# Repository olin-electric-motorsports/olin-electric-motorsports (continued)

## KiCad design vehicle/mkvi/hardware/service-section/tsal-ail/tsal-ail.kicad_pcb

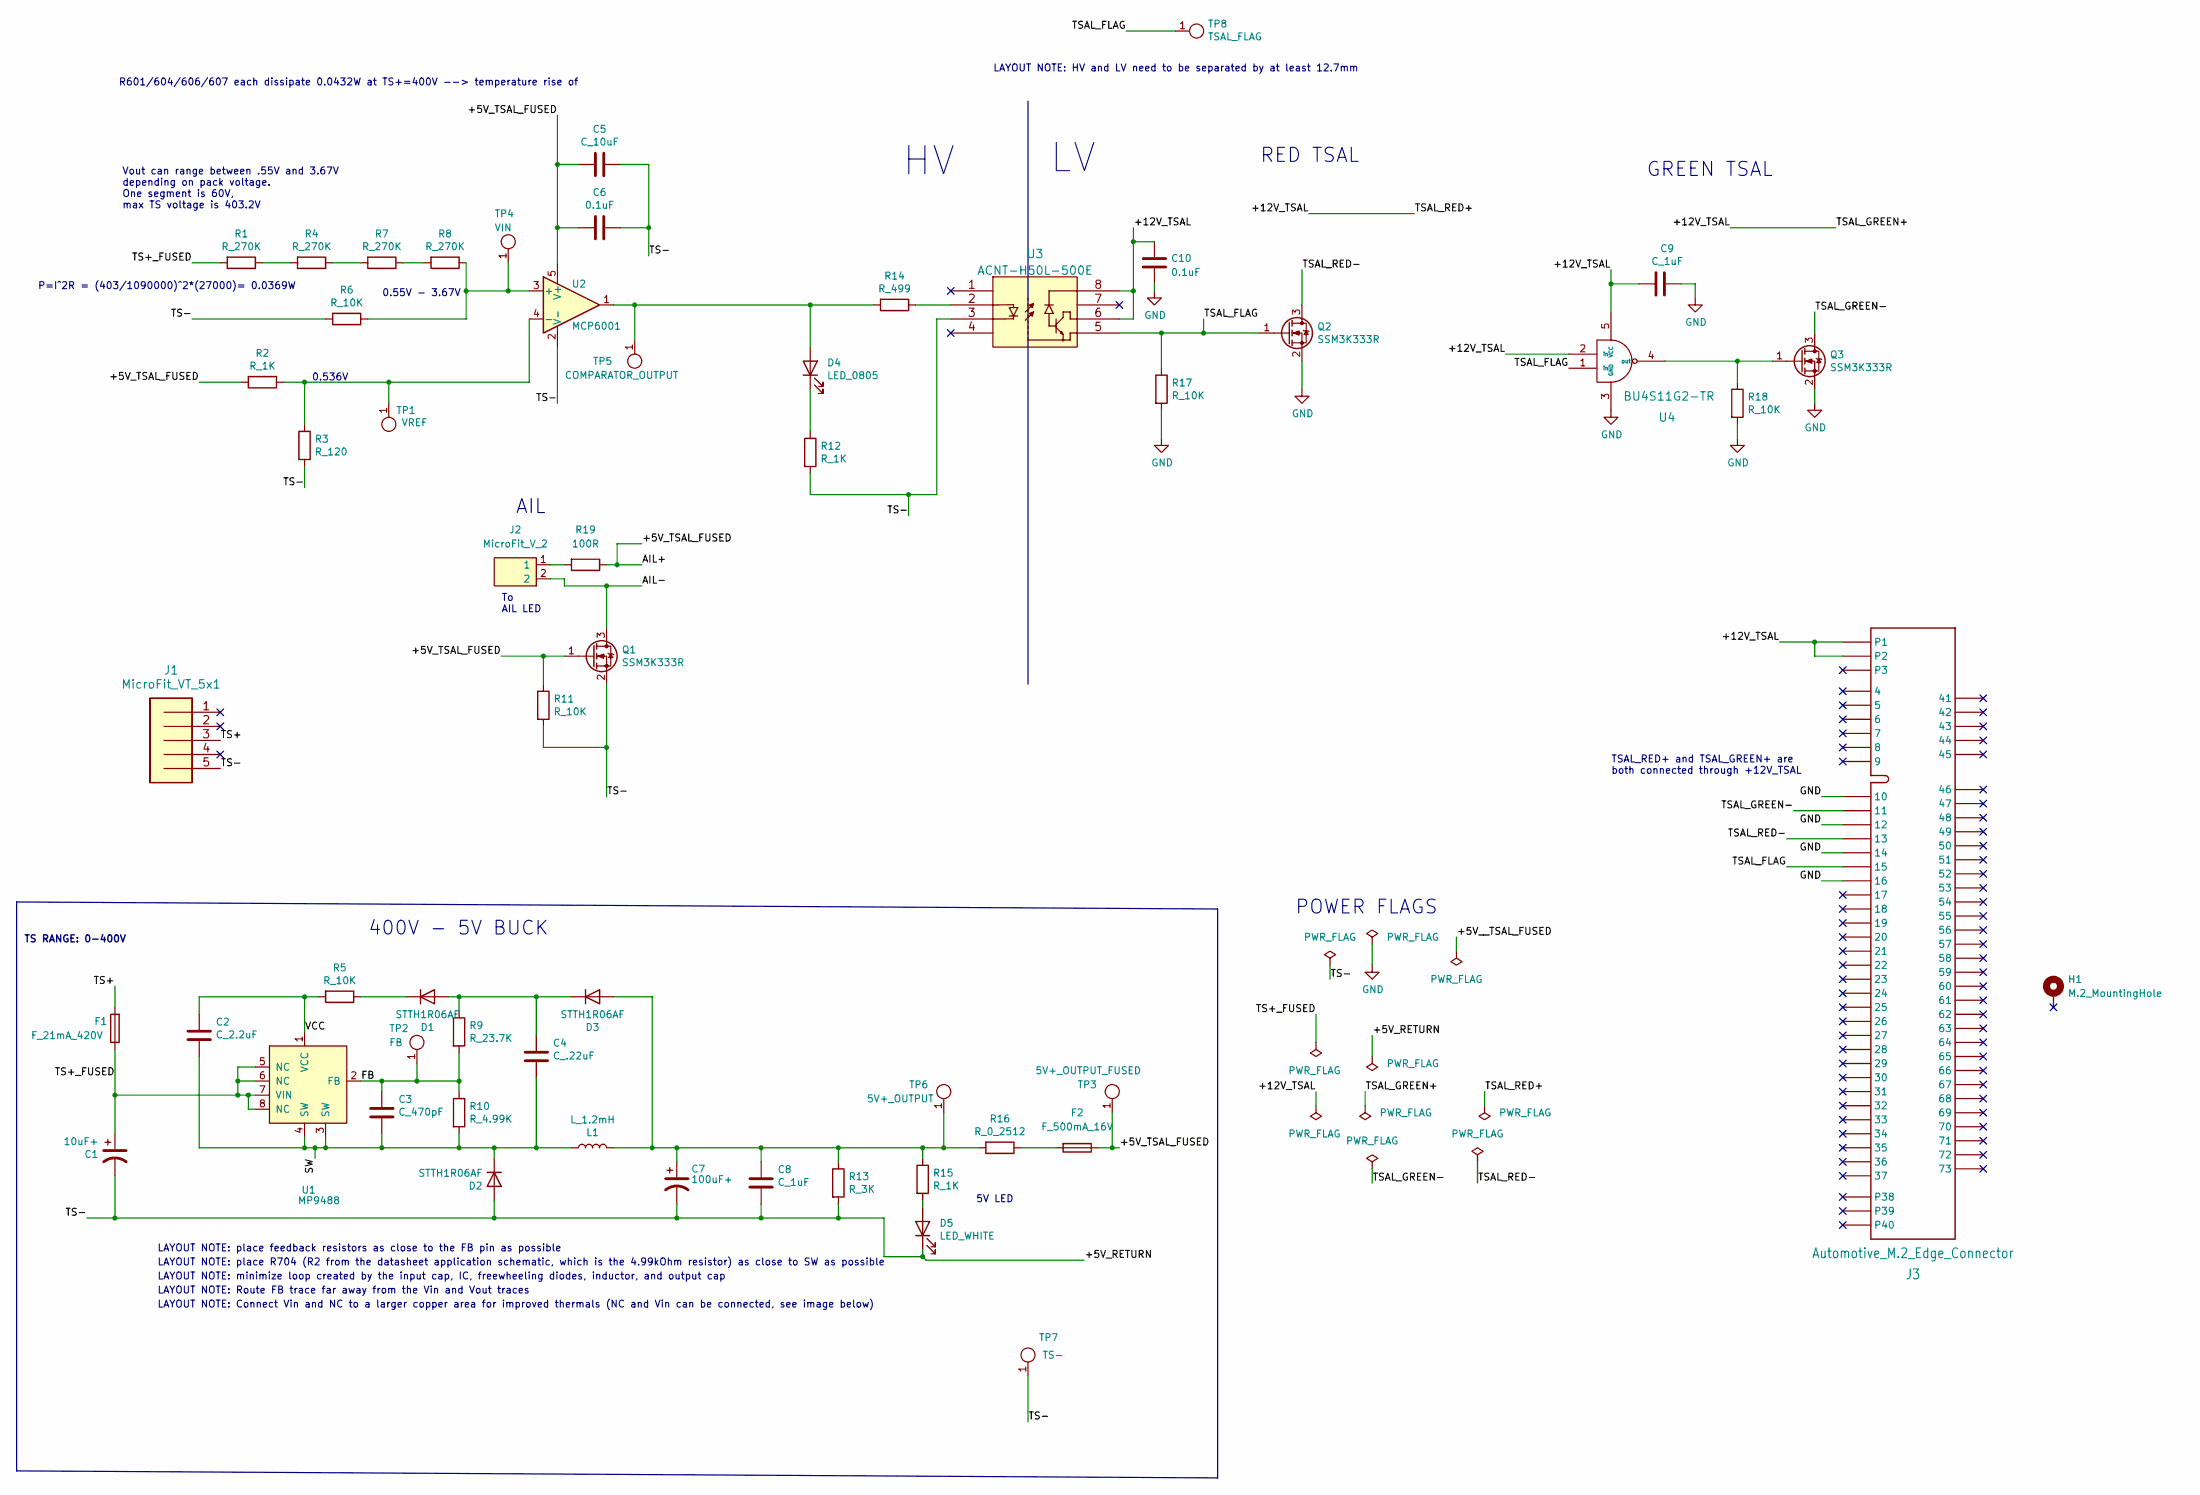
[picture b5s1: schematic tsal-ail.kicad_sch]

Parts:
C1: 10uF+; CP_Radial_D10.0mm_P5.00mm; MPN 450BXC10MEFC10X20
C2: C_2.2uF; C_0603; MPN GRM188R61E225KA12J
C3: C_470pF; C_0603; MPN 0603B471K500CT
C4: C_.22uF; C_0603; MPN CL10A224KB8NNNC
C5: C_10uF; C_0603; MPN LMK107BBJ106KALT
C6, C10: 0.1uF; C_0603; MPN CL10B104KB8NNWC
C7: 100uF+; CP_Radial_D8.0mm_P3.50mm; MPN ESK107M050AG3EA
C8, C9: C_1uF; C_0603; MPN CL10B105KA8NNNC
D1, D2, D3: STTH1R06AF; D_SOD-128; MPN STTH1R06AF
D4: LED_0805; CHIPLED_0805; MPN LTST-C170KFKT
D5: LED_WHITE; CHIPLED_0805; MPN B1701TW--20P000314U1930
F1: F_21mA_420V; MPN B59884C0120A054
F2: F_500mA_16V; Fuse_1210; MPN 0ZCH0050FF2G
H1: M.2_MountingHole; M.2_Mount
J1: MicroFit_VT_5x1; Connector_MicroFit_VT_5x1; MPN 436500515
J2: MicroFit_V_2; MPN 0430450212
J3: Automotive_M.2_Edge_Connector; MPN N/A
L1: L_1.2mH; MPN RCP1317NP-122L
Q1, Q2, Q3: SSM3K333R; SOT-23F; MPN SSM3K333R,LF
R1, R4, R7, R8: R_270K; R_0603; MPN RMCF0603FT270K
R2, R12, R15: R_1K; R_0603; MPN RMCF0603FT1K00
R3: R_120; R_0603; MPN RC0603FR-13120RL
R5, R6, R11, R17, R18: R_10K; R_0603; MPN RMCF0603FT10K0
R9: R_23.7K; R_0603; MPN RMCF0603FT23K7
R10: R_4.99K; R_0603; MPN RMCF0603FT4K99
R13: R_3K; R_0603; MPN RC0603FR-103KL
R14: R_499; R_0603; MPN RC0603FR-10499RL
R16: R_0_2512; R_2512_6332Metric; MPN CR2512-J/-000ELF
R19: 100R; R_0603; MPN RMCF0603FT100R
TP1: VREF; TestPoint_Pad_D1.0mm
TP2: FB; TestPoint_Pad_D1.0mm
TP3: 5V+_OUTPUT_FUSED; TestPoint_Pad_D1.0mm
TP4: VIN; TestPoint_Pad_D1.0mm
TP5: COMPARATOR_OUTPUT; TestPoint_Pad_D1.0mm
TP6: 5V+_OUTPUT; TestPoint_Pad_D1.0mm
TP7: TS-; TestPoint_Pad_D2.0mm
TP8: TSAL_FLAG; TestPoint_Pad_D1.0mm
U1: MP9488; Converter_DCDC_MPS_MP9488; MPN MP9488GS-Z
U2: MCP6001; SOT-353_SC-70-5; MPN MCP6001T-I/OT
U3: ACNT-H50L-500E; MPN ACNT-H50L-000E
U4: BU4S11G2-TR; SSOP5; MPN BU4S11G2-TR

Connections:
/+5V_RETURN: C1.2, C5.1, C6.1, C7.2, C8.2, D2.2 (A), D5.1 (K), J1.5, Q1.2 (S), R3.2, R6.2, R11.2, R12.2, R13.2, TP7.1, U2.2 (V-), U3.3
/+5V_TSAL_FUSED: C5.2, C6.2, F2.1, Q1.1 (G), R2.2, R11.1, R19.1, TP3.1, U2.5 (V+)
/+12V_TSAL: C9.2, C10.1, J3.P1, J3.P2, U3.6, U3.8, U4.2 (in), U4.5 (VCC)
/AIL-: J2.2, Q1.3 (D)
/FB: C3.1, R9.2, R10.1, TP2.1, U1.2 (FB)
/SW: C2.2, C3.2, C4.2, D2.1 (K), L1.1, R10.2, U1.3 (SW), U1.4 (SW)
/TS+: F1.2, J1.3
/TS+_FUSED: C1.1, F1.1, R1.2, U1.5 (NC), U1.6 (NC), U1.7 (VIN), U1.8 (NC)
/TSAL_FLAG: J3.15, Q2.1 (G), R17.1, TP8.1, U3.5, U4.1 (in)
/TSAL_GREEN-: J3.11, Q3.3 (D)
/TSAL_RED-: J3.13, Q2.3 (D)
/VCC: C2.1, R5.2, U1.1 (VCC)
GND: C9.1, C10.2, J3.10, J3.12, J3.14, J3.16, Q2.2 (S), Q3.2 (S), R17.2, R18.2, U4.3 (GND)
unnamed: C4.1, D1.2 (A), D3.1 (K), R9.1
unnamed: C7.1, C8.1, D3.2 (A), L1.2, R13.1, R15.1, R16.2, TP6.1
unnamed: D1.1 (K), R5.1
unnamed: D4.1 (K), R12.1
unnamed: D4.2 (A), R14.2, TP5.1, U2.1
unnamed: D5.2 (A), R15.2
unnamed: F2.2, R16.1
unnamed: J2.1, R19.2
unnamed: Q3.1 (G), R18.1, U4.4 (out)
unnamed: R1.1, R4.2
unnamed: R2.1, R3.1, TP1.1, U2.4 (-)
unnamed: R4.1, R7.2
unnamed: R6.1, R8.1, TP4.1, U2.3 (+)
unnamed: R7.1, R8.2
unnamed: R14.1, U3.2

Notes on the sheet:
TSAL_RED+ and TSAL_GREEN+ are both connected through +12V_TSAL
LAYOUT NOTE: Route FB trace far away from the Vin and Vout traces
AIL
LAYOUT NOTE: minimize loop created by the input cap, IC, freewheeling diodes, inductor, and output cap
RED TSAL
LAYOUT NOTE: Connect Vin and NC to a larger copper area for improved thermals (NC and Vin can be connected, see image below)
GREEN TSAL
P=I^2R = (403/1090000)^2*(27000)= 0.0369W
LAYOUT NOTE: place feedback resistors as close to the FB pin as possible
Vout can range between .55V and 3.67V depending on pack voltage. One segment is 60V, max TS voltage is 403.2V
LAYOUT NOTE: place R704 (R2 from the datasheet application schematic, which is the 4.99kOhm resistor) as close to SW as possible
LAYOUT NOTE: HV and LV need to be separated by at least 12.7mm
5V LED
POWER FLAGS
0.536V
R601/604/606/607 each dissipate 0.0432W at TS+=400V --> temperature rise of
0.55V - 3.67V
TS RANGE: 0-400V
To AIL LED
400V - 5V BUCK

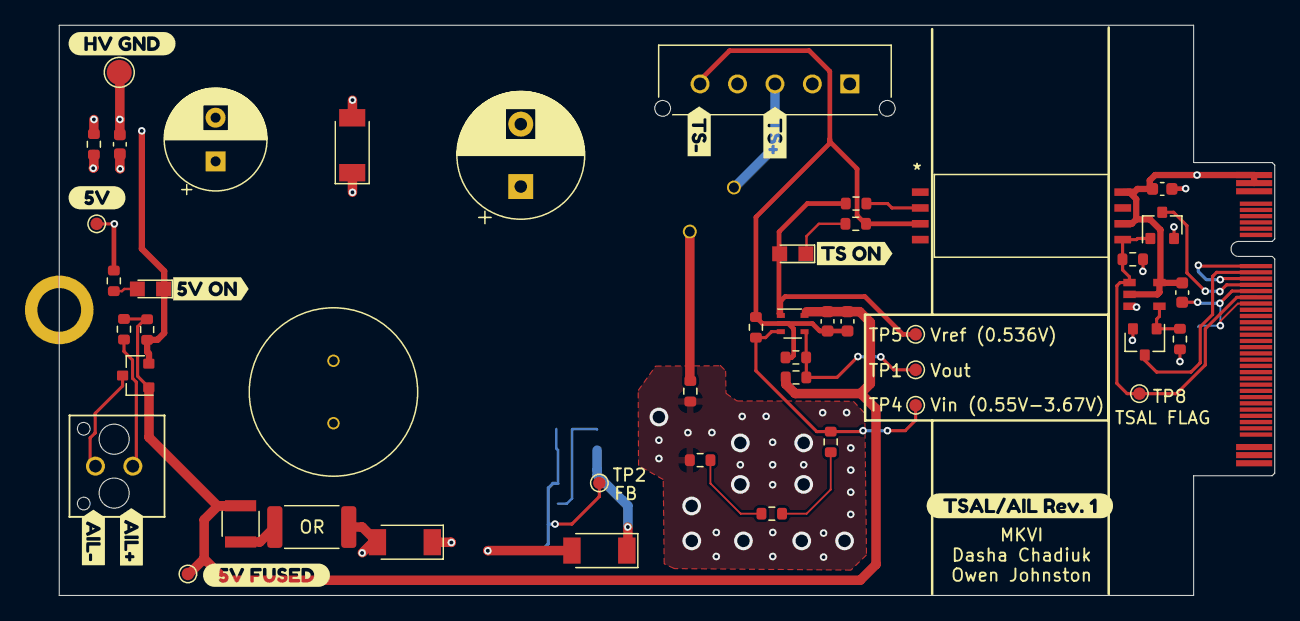
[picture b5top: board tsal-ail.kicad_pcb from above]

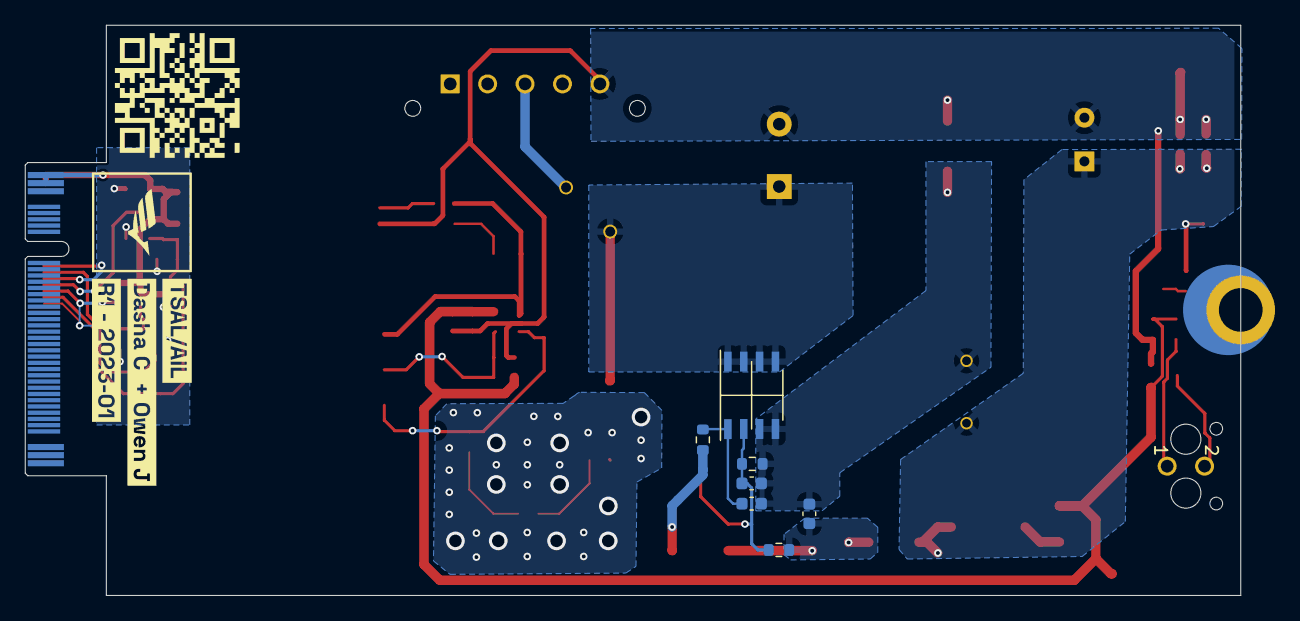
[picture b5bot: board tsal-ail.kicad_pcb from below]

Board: 2 copper layers, 97.4 x 45.7 mm, 70 parts (11 on the bottom side), 28 nets.

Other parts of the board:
QR*****: hw.oem.to/6_TSAL-AIL_1; QR_6_TSAL-AIL_1
kibuzzard-63AC91FD: G***; kibuzzard-63AC91FD
kibuzzard-63AC92E3: G***; kibuzzard-63AC92E3
kibuzzard-63AC93EB: G***; kibuzzard-63AC93EB
kibuzzard-63AC93FC: G***; kibuzzard-63AC93FC
kibuzzard-63AC9220: G***; kibuzzard-63AC9220
kibuzzard-63AC9283: G***; kibuzzard-63AC9283
kibuzzard-63AC9446: G***; kibuzzard-63AC9446
kibuzzard-63AC9456: G***; kibuzzard-63AC9456
kibuzzard-63AD023E: G***; kibuzzard-63AD023E
kibuzzard-63AD0077: G***; kibuzzard-63AD0077
kibuzzard-63BF4696: G***; kibuzzard-63BF4696
kibuzzard-63D843BA: G***; kibuzzard-63D843BA
kibuzzard-63D84460: G***; kibuzzard-63D84460

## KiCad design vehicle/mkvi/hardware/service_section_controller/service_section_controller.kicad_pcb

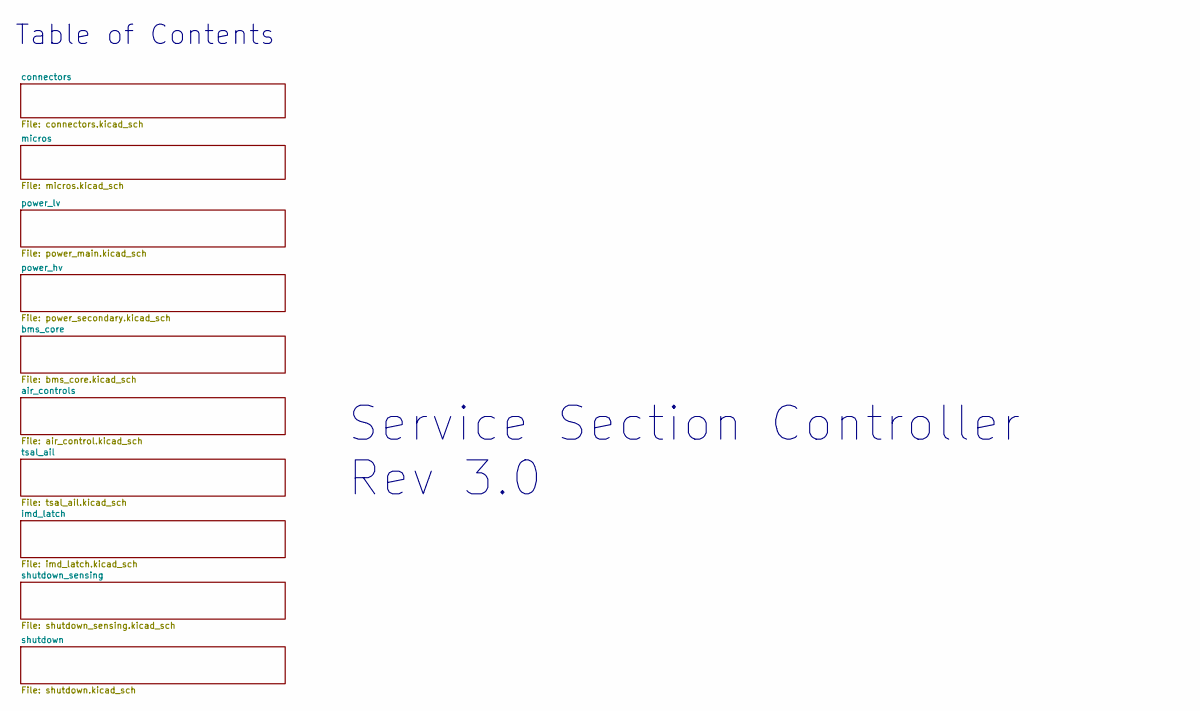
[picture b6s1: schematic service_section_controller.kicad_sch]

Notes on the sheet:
Table of Contents
Service Section Controller Rev 3.0

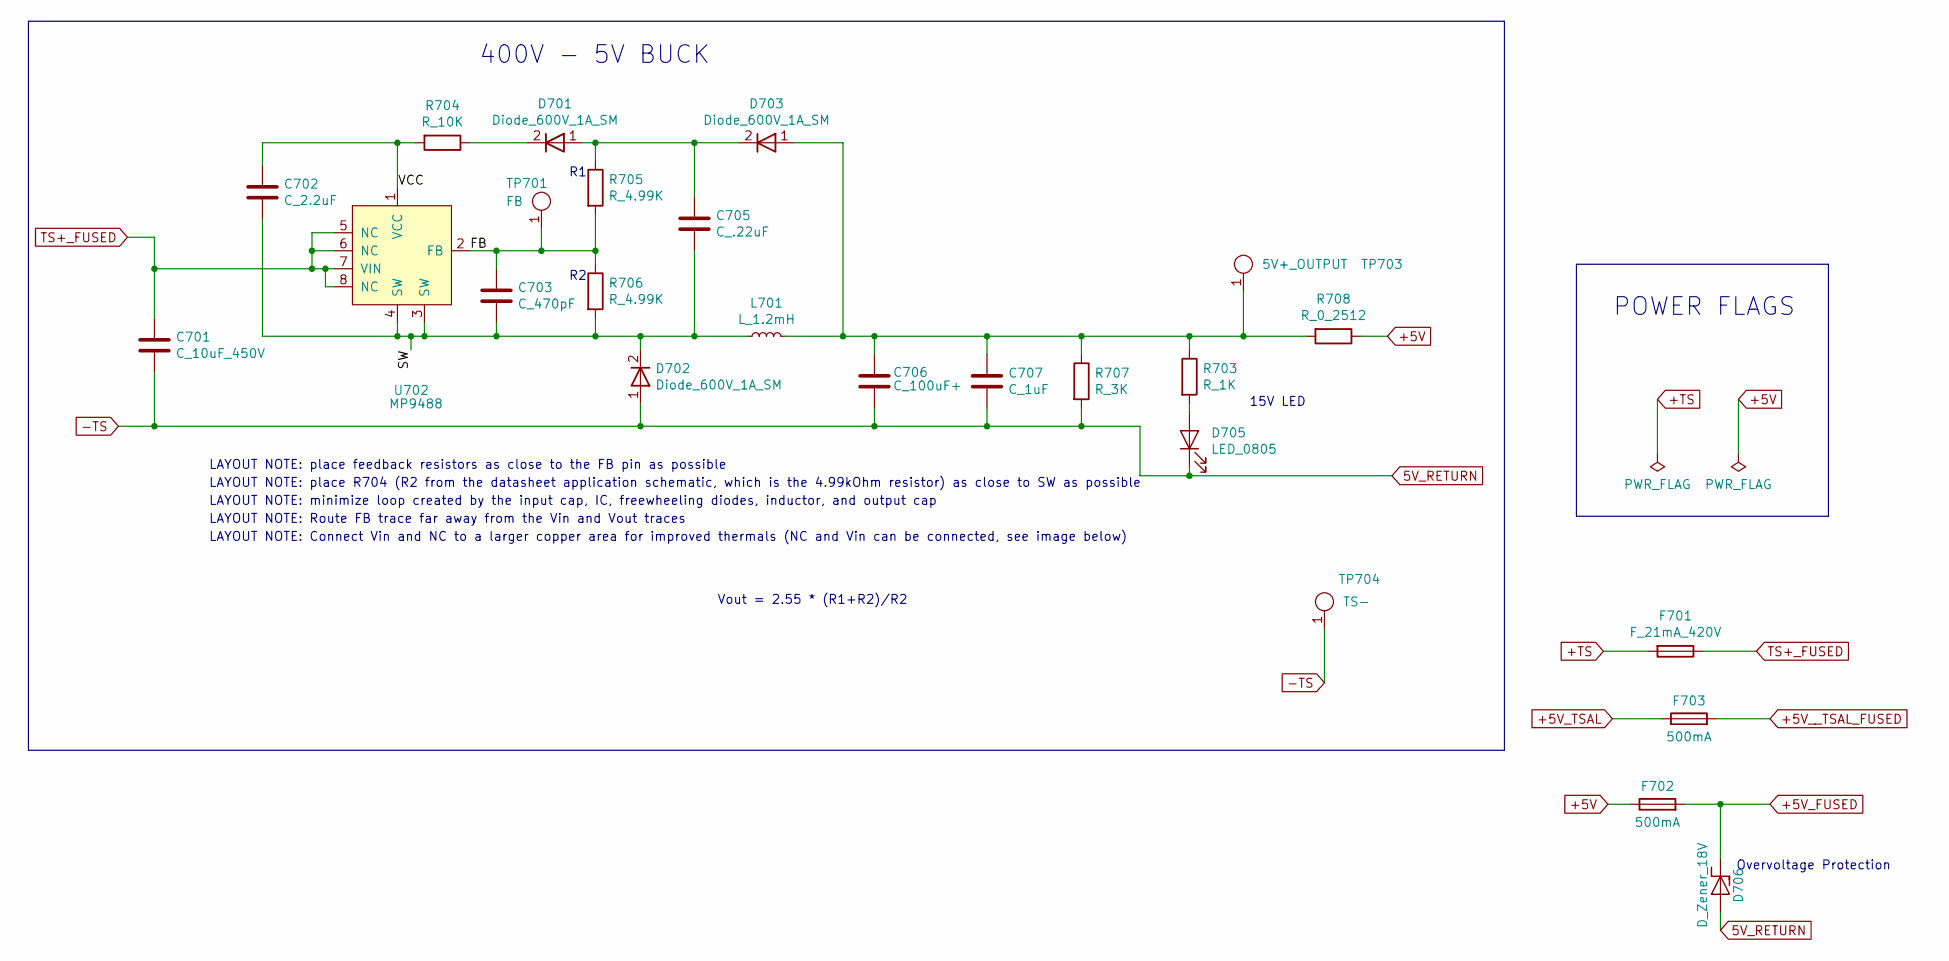
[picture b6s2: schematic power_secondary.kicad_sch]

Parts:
C701: C_10uF_450V
C702: C_2.2uF; C_0805_OEM
C703: C_470pF; C_0805_OEM
C705: C_.22uF; C_0805_OEM
C706: C_100uF+
C707: C_1uF; C_0805_OEM
D701, D702, D703: Diode_600V_1A_SM
D705: LED_0805; LED_0805_OEM; MPN 475-1410-1-ND
D706: D_Zener_18V; DO-214AA; MPN SMBJ5355B-TPMSCT-ND
F701: F_21mA_420V; MPN 495-75309-ND
F702, F703: 500mA; Fuse_1210; MPN 507-1786-1-ND
L701: L_1.2mH
R703: R_1K; R_0805_OEM; MPN RNCP0805FTD1K00CT-ND
R704: R_10K; R_0805_OEM; MPN CRS0805-FX-1002ELFCT-ND
R705: R_4.99K; R_0805_OEM; MPN P21173CT-ND
R706: R_4.99K; R_0805_OEM; MPN RNCP0805FTD4K99CT-ND
R707: R_3K; R_0805_OEM; MPN RMCF0805FT3K00CT-ND
R708: R_0_2512; R_2512_OEM; MPN A121322CT-ND
TP701: FB; TestPoint_Pad_D1.0mm
TP703: 5V+_OUTPUT; TestPoint_Pad_D1.0mm
TP704: TS-; TestPoint_Pad_D2.0mm
U702: MP9488; Converter_DCDC_MPS_MP9488

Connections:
+5V: F702.1, R708.1; also elsewhere on the board
+5V_FUSED: D706.1 (K), F702.2; also elsewhere on the board
+5V_TSAL: F703.1
+5V__TSAL_FUSED: F703.2; also elsewhere on the board
+TS: F701.2; also elsewhere on the board
-TS: C701.1, C706.2, C707.2, D702.1, D705.1 (K), D706.2 (A), R707.2, TP704.1; also elsewhere on the board
/power_hv/FB: C703.1, R705.2, R706.1, TP701.1, U702.2 (FB)
/power_hv/SW: C702.2, C703.2, C705.2, D702.2, L701.1, R706.2, U702.3 (SW), U702.4 (SW)
/power_hv/VCC: C702.1, R704.2, U702.1 (VCC)
unnamed: C705.1, D701.1, D703.2, R705.1
unnamed: C706.1, C707.1, D703.1, L701.2, R703.1, R707.1, R708.2, TP703.1
unnamed: D701.2, R704.1
unnamed: D705.2 (A), R703.2
TS+_FUSED: C701.2, F701.1, U702.5 (NC), U702.6 (NC), U702.7 (VIN), U702.8 (NC); also elsewhere on the board

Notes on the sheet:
LAYOUT NOTE: Connect Vin and NC to a larger copper area for improved thermals (NC and Vin can be connected, see image below)
400V - 5V BUCK
LAYOUT NOTE: minimize loop created by the input cap, IC, freewheeling diodes, inductor, and output cap
LAYOUT NOTE: Route FB trace far away from the Vin and Vout traces
LAYOUT NOTE: place R704 (R2 from the datasheet application schematic, which is the 4.99kOhm resistor) as close to SW as possible
Overvoltage Protection
15V LED
LAYOUT NOTE: place feedback resistors as close to the FB pin as possible
Vout = 2.55 * (R1+R2)/R2
POWER FLAGS

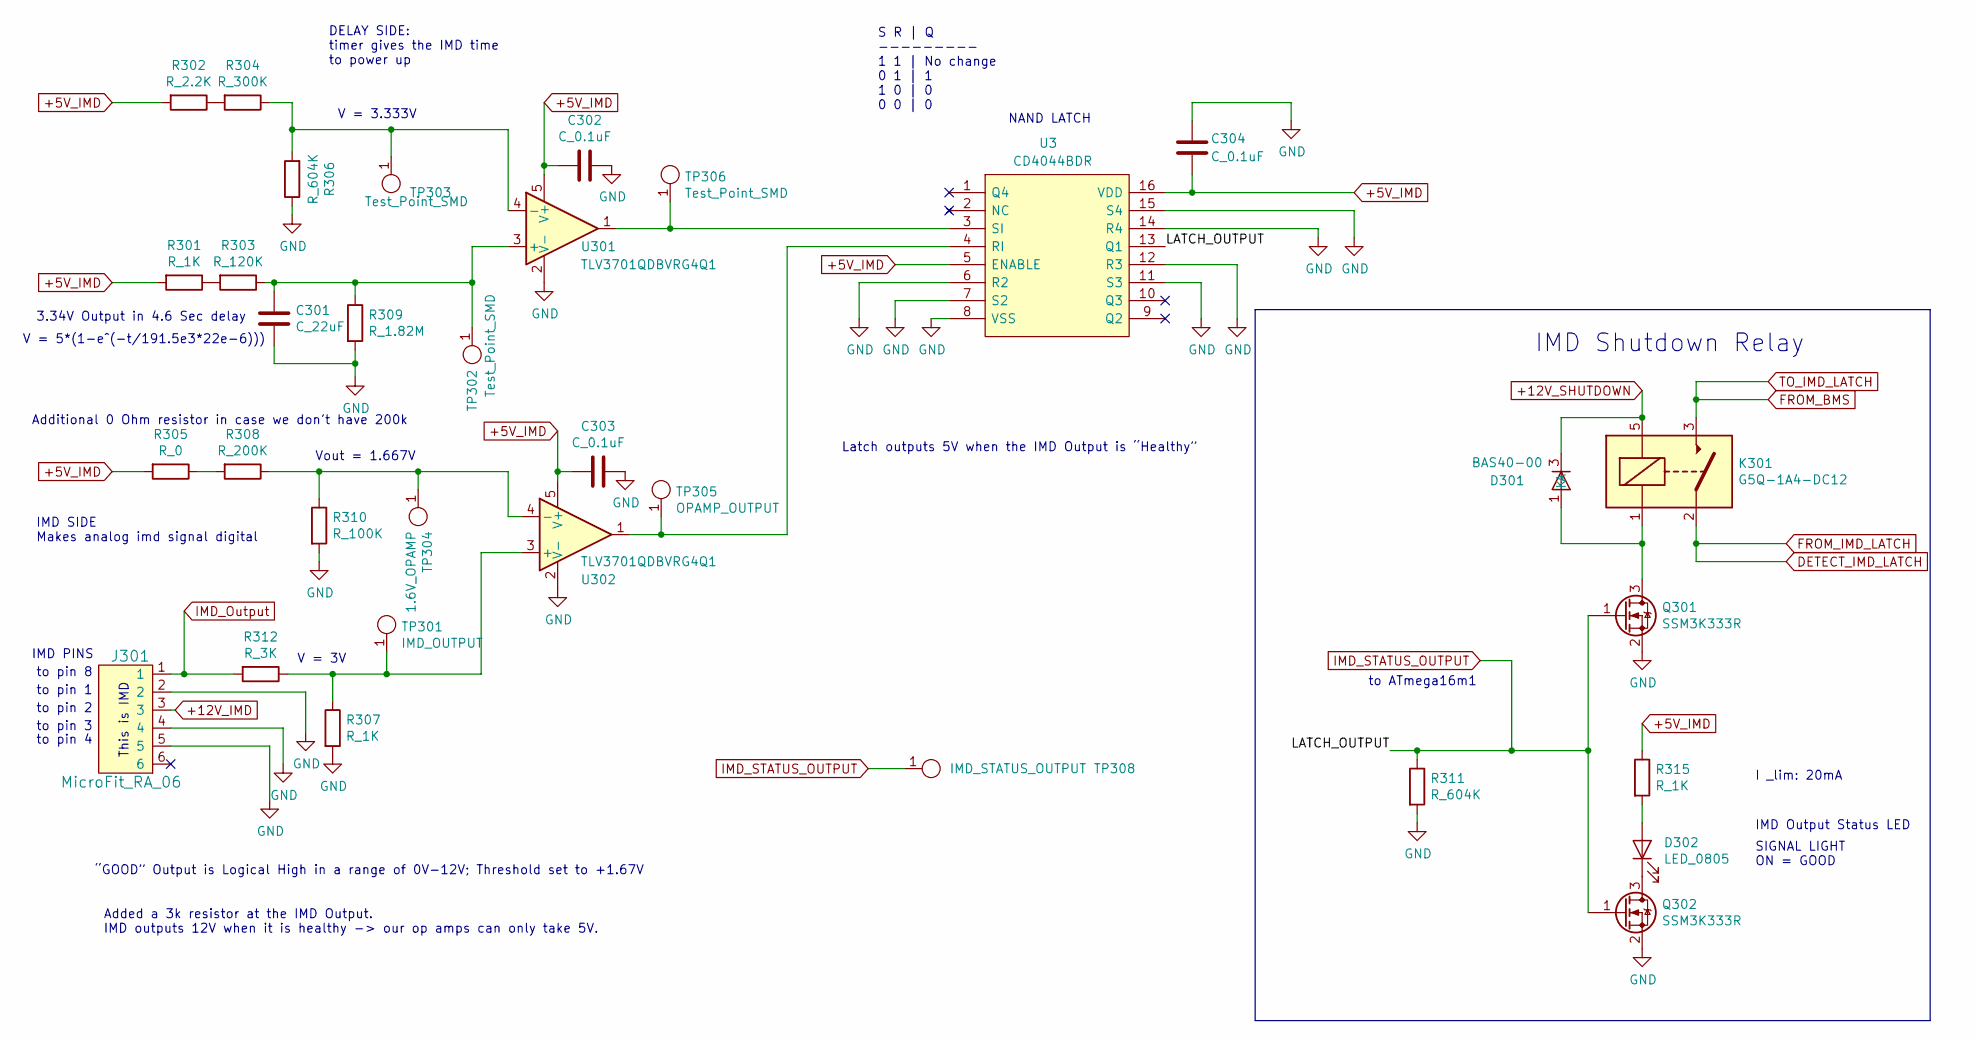
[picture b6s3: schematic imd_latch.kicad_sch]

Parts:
C301: C_22uF; C_1206_OEM; MPN 445-11693-1-ND
C302, C303, C304: C_0.1uF; C_0805_OEM; MPN 478-3352-1-ND
D301: BAS40-00; SOT-23; MPN 1727-4234-1-ND
D302: LED_0805; LED_0805_OEM; MPN 475-1410-1-ND
J301: MicroFit_RA_06; 430450602; MPN WM4037-ND
K301: G5Q-1A4-DC12; Relay_SPST_OMRON-G5Q-1A4_OEM
Q301, Q302: SSM3K333R; SOT-23F; MPN SSM3K333RLFCT-ND
R301, R307, R315: R_1K; R_0805_OEM; MPN RNCP0805FTD1K00CT-ND
R302: R_2.2K; R_0805_OEM; MPN RMCF0805FT2K20CT-ND
R303: R_120K; R_0805_OEM; MPN RMCF0805FT120KCT-ND
R304: R_300K; R_0805_OEM; MPN P300KDACT-ND
R305: R_0; R_0603_1608Metric; MPN P0.0GCT-ND
R306, R311: R_604K; R_0805_OEM; MPN RMCF0805FT604KCT-ND
R308: R_200K; R_0805_OEM; MPN P300KDACT-ND
R309: R_1.82M; R_0805_OEM; MPN RMCF0805FT1M82CT-ND
R310: R_100K; R_0805_OEM; MPN P100KCCT-ND
R312: R_3K; R_0805_OEM; MPN RMCF0805FT3K00CT-ND
TP301: IMD_OUTPUT; TestPoint_Pad_D1.0mm
TP302, TP303, TP306: Test_Point_SMD; TestPoint_Pad_D1.0mm
TP304: 1.6V_OPAMP; TestPoint_Pad_D1.0mm
TP305: OPAMP_OUTPUT; TestPoint_Pad_D1.0mm
TP308: IMD_STATUS_OUTPUT; TestPoint_Pad_D1.0mm
U3: CD4044BDR; SOIC127P600X175-16N; MPN 296-31498-1-ND; Mouser Part Number 595-CD4044BDR
U301, U302: TLV3701QDBVRG4Q1; SOT-23-5_OEM; MPN 497-10249-1-ND

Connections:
+5V_IMD: C302.2, C303.2, C304.2, R301.2, R302.2, R305.2, R315.1, U3.5 (ENABLE), U3.16 (VDD), U301.5 (V+), U302.5 (V+); also elsewhere on the board
+12V_IMD: J301.3; also elsewhere on the board
+12V_SHUTDOWN: D301.3 (K), K301.5; also elsewhere on the board
+AIR_COIL_-: C301.2, C302.1, C303.1, C304.1, J301.2, J301.4, J301.5, Q301.2 (S), Q302.2 (S), R306.1, R307.2, R309.2, R310.2, R311.2, U3.6 (R2), U3.7 (S2), U3.8 (VSS), U3.11 (S3), U3.12 (R3), U3.14 (R4), U3.15 (S4), U301.2 (V-), U302.2 (V-); also elsewhere on the board
DETECT_BMS: K301.3; also elsewhere on the board
DETECT_IMD_LATCH: K301.2; also elsewhere on the board
IMD_Output: J301.1, R312.2
IMD_STATUS_OUTPUT: Q301.1 (G), Q302.1 (G), R311.1, TP308.1, U3.13 (Q1); also elsewhere on the board
unnamed: C301.1, R303.1, R309.1, TP302.1, U301.3 (+)
unnamed: D301.1 (A), K301.1, Q301.3 (D)
unnamed: D302.1 (K), Q302.3 (D)
unnamed: D302.2 (A), R315.2
unnamed: R301.1, R303.2
unnamed: R302.1, R304.2
unnamed: R304.1, R306.2, TP303.1, U301.4 (-)
unnamed: R305.1, R308.2
unnamed: R307.1, R312.1, TP301.1, U302.3 (+)
unnamed: R308.1, R310.1, TP304.1, U302.4 (-)
unnamed: TP305.1, U3.4 (RI), U302.1
unnamed: TP306.1, U3.3 (SI), U301.1

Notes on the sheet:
Vout = 1.667V
DELAY SIDE: timer gives the IMD time to power up
Added a 3k resistor at the IMD Output. IMD outputs 12V when it is healthy -> our op amps can only take 5V.
SIGNAL LIGHT ON = GOOD
I _lim: 20mA
to pin 2
NAND LATCH
to pin 4
V = 5*(1-e^(-t/191.5e3*22e-6)))
S R | Q --------- 1 1 | No change 0 1 | 1 1 0 | 0 0 0 | 0
to pin 3
Additional 0 Ohm resistor in case we don't have 200k
IMD Shutdown Relay
to pin 1
3.34V Output in 4.6 Sec delay
V = 3.333V
Latch outputs 5V when the IMD Output is “Healthy”
This is IMD
IMD PINS
IMD SIDE Makes analog imd signal digital
“GOOD” Output is Logical High in a range of 0V-12V; Threshold set to +1.67V
V = 3V
to pin 8
IMD Output Status LED
to ATmega16m1

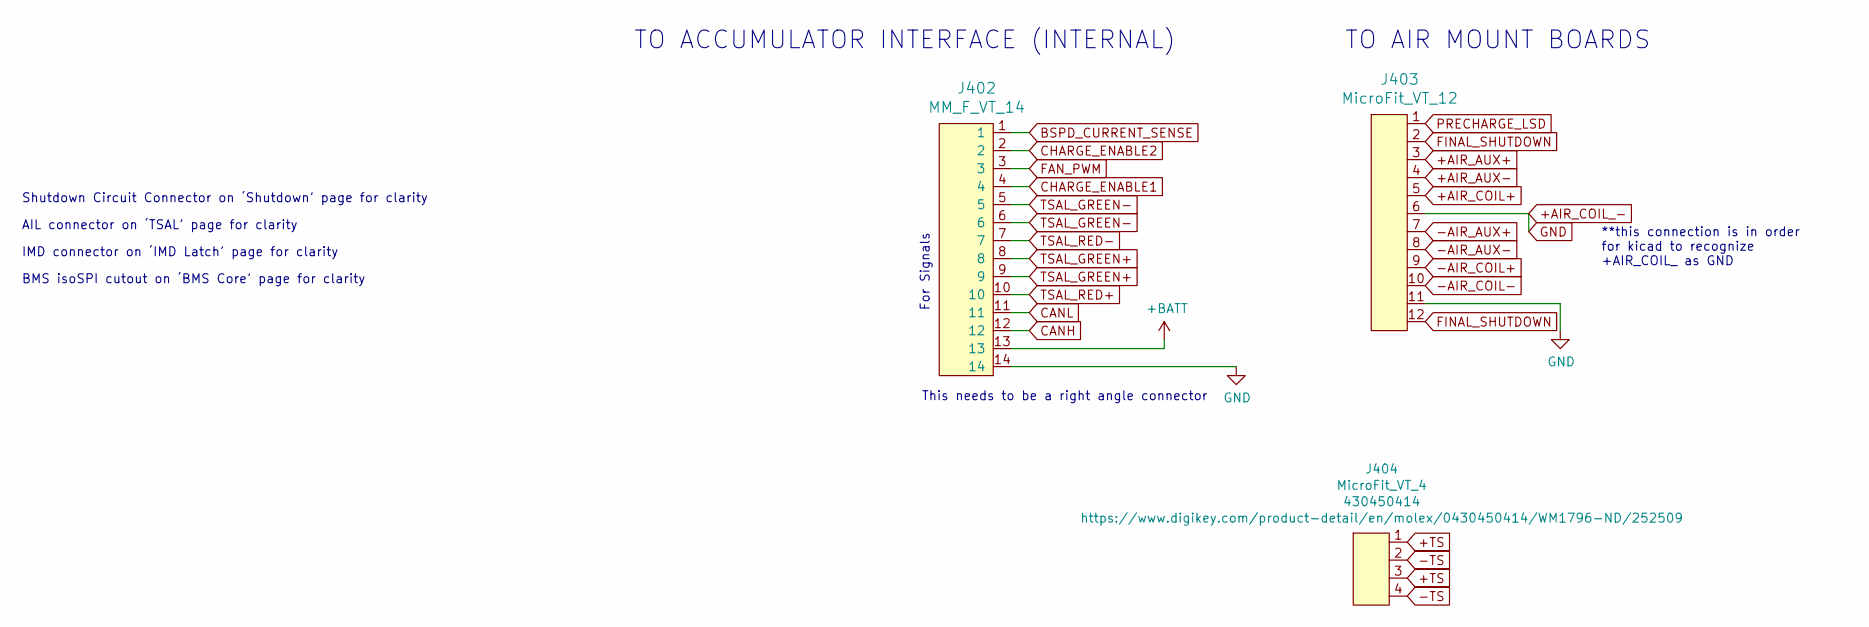
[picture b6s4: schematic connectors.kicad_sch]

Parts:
J402: MM_F_VT_14; micromatch_female_vert_14; MPN 1-338068-4
J403: MicroFit_VT_12
J404: MicroFit_VT_4; MPN 430450414

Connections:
+12V_TSAL: J402.8, J402.9, J402.10; also elsewhere on the board
+AIR_AUX-: J403.4; also elsewhere on the board
+AIR_COIL+: J403.2, J403.5, J403.9, J403.12; also elsewhere on the board
+AIR_COIL_-: J402.14, J403.6, J403.11; also elsewhere on the board
+BATT: J402.13; also elsewhere on the board
+TS: J404.1, J404.3; also elsewhere on the board
-AIR_AUX-: J403.8; also elsewhere on the board
-AIR_COIL-: J403.10; also elsewhere on the board
-TS: J404.2, J404.4; also elsewhere on the board
BSPD_CURRENT_SENSE: J402.1; also elsewhere on the board
CANH: J402.12; also elsewhere on the board
CANL: J402.11; also elsewhere on the board
CHARGE_ENABLE1: J402.4; also elsewhere on the board
CHARGE_ENABLE2: J402.2; also elsewhere on the board
PRECHARGE_LSD: J403.1; also elsewhere on the board
TSAL_GREEN-: J402.5, J402.6; also elsewhere on the board
TSAL_RED-: J402.7; also elsewhere on the board

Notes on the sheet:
BMS isoSPI cutout on ‘BMS Core’ page for clarity
AIL connector on ‘TSAL’ page for clarity
For Signals
**this connection is in order for kicad to recognize +AIR_COIL_ as GND
TO AIR MOUNT BOARDS
IMD connector on ‘IMD Latch’ page for clarity
This needs to be a right angle connector
TO ACCUMULATOR INTERFACE (INTERNAL)
Shutdown Circuit Connector on ‘Shutdown’ page for clarity

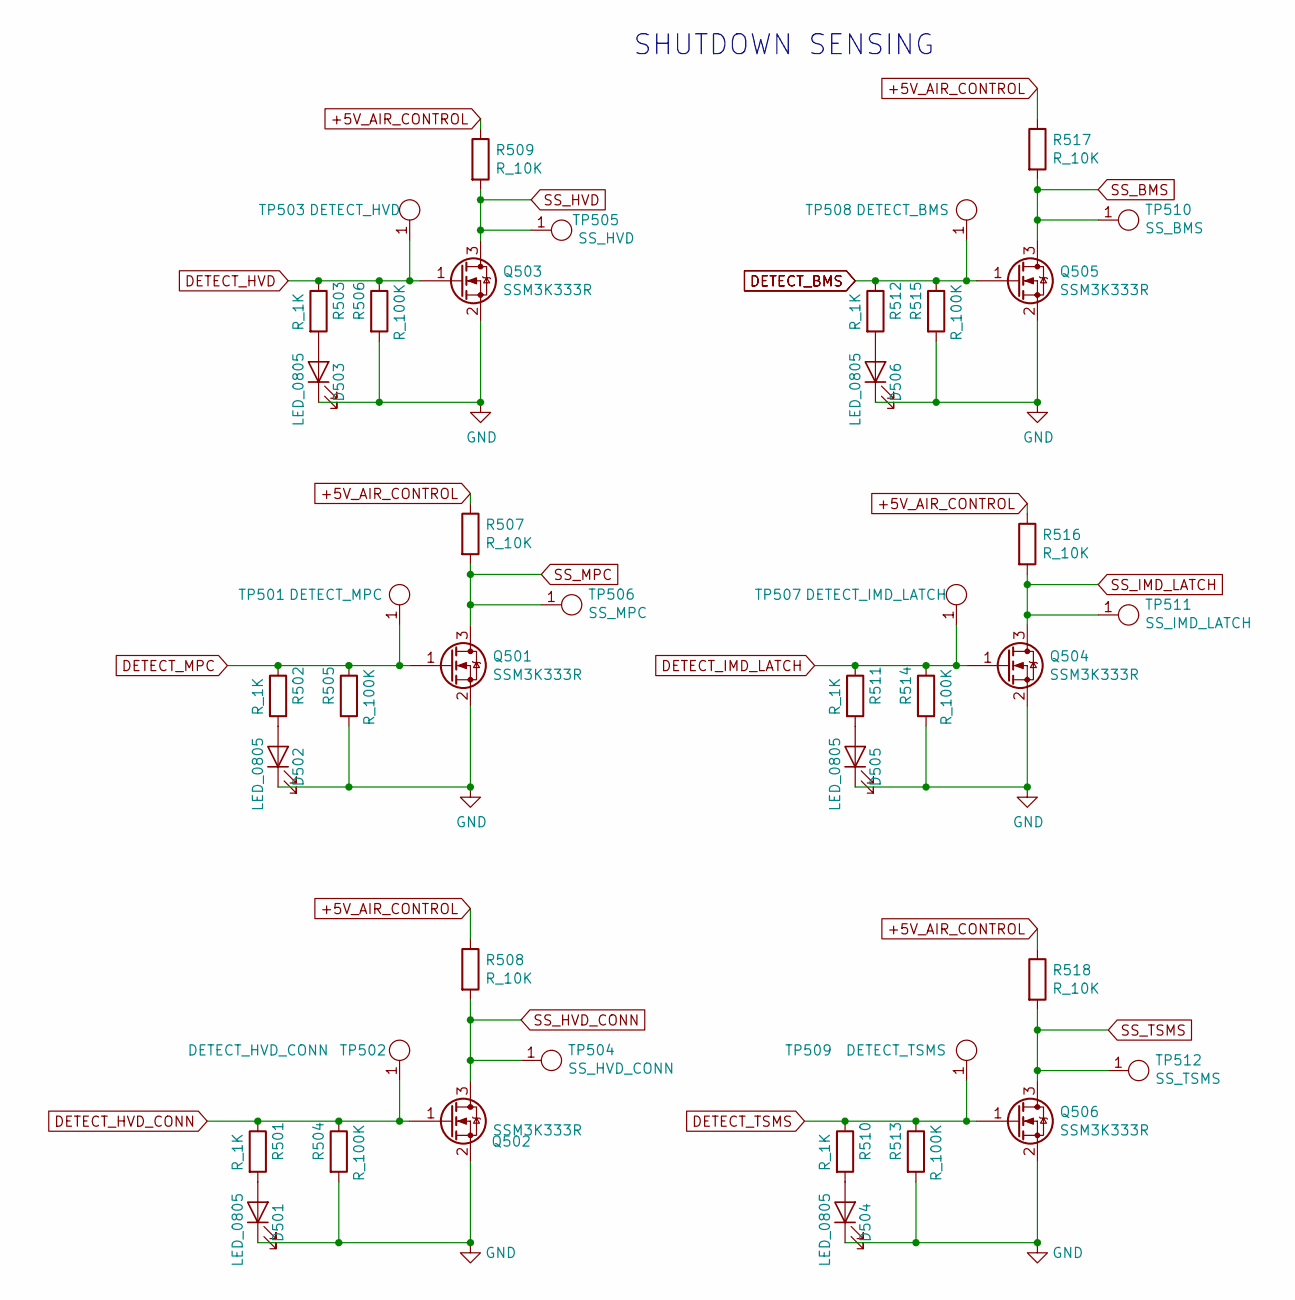
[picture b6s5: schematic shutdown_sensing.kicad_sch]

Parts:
D501, D502, D503, D504, D505, D506: LED_0805; LED_0805_OEM; MPN 475-1410-1-ND
Q501, Q502, Q503, Q504, Q505, Q506: SSM3K333R; SOT-23F; MPN SSM3K333RLFCT-ND
R501, R502, R503, R510, R511, R512: R_1K; R_0805_OEM; MPN RNCP0805FTD1K00CT-ND
R504, R505, R506, R513, R514, R515: R_100K; R_0805_OEM; MPN P100KCCT-ND
R507, R508, R509, R516, R517, R518: R_10K; R_0805_OEM; MPN CRS0805-FX-1002ELFCT-ND
TP501: DETECT_MPC; TestPoint_Pad_D1.0mm
TP502: DETECT_HVD_CONN; TestPoint_Pad_D1.0mm
TP503: DETECT_HVD; TestPoint_Pad_D1.0mm
TP504: SS_HVD_CONN; TestPoint_Pad_D1.0mm
TP505: SS_HVD; TestPoint_Pad_D1.0mm
TP506: SS_MPC; TestPoint_Pad_D1.0mm
TP507: DETECT_IMD_LATCH; TestPoint_Pad_D1.0mm
TP508: DETECT_BMS; TestPoint_Pad_D1.0mm
TP509: DETECT_TSMS; TestPoint_Pad_D1.0mm
TP510: SS_BMS; TestPoint_Pad_D1.0mm
TP511: SS_IMD_LATCH; TestPoint_Pad_D1.0mm
TP512: SS_TSMS; TestPoint_Pad_D1.0mm

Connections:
+AIR_COIL_-: D501.1 (K), D502.1 (K), D503.1 (K), D504.1 (K), D505.1 (K), D506.1 (K), Q501.2 (S), Q502.2 (S), Q503.2 (S), Q504.2 (S), Q505.2 (S), Q506.2 (S), R504.2, R505.2, R506.2, R513.2, R514.2, R515.2; also elsewhere on the board
DETECT_BMS: Q505.1 (G), R512.1, R515.1, TP508.1; also elsewhere on the board
DETECT_HVD: Q503.1 (G), R503.1, R506.1, TP503.1; also elsewhere on the board
DETECT_HVD_CONN: Q502.1 (G), R501.1, R504.1, TP502.1; also elsewhere on the board
DETECT_IMD_LATCH: Q504.1 (G), R511.1, R514.1, TP507.1; also elsewhere on the board
DETECT_TSMS: Q506.1 (G), R510.1, R513.1, TP509.1; also elsewhere on the board
unnamed: D501.2 (A), R501.2
unnamed: D502.2 (A), R502.2
unnamed: D503.2 (A), R503.2
unnamed: D504.2 (A), R510.2
unnamed: D505.2 (A), R511.2
unnamed: D506.2 (A), R512.2
SS_BMS: Q505.3 (D), R517.2, TP510.1; also elsewhere on the board
SS_HVD: Q503.3 (D), R509.2, TP505.1; also elsewhere on the board
SS_HVD_CONN: Q502.3 (D), R508.2, TP504.1; also elsewhere on the board
SS_IMD_LATCH: Q504.3 (D), R516.2, TP511.1; also elsewhere on the board
SS_MPC: Q501.3 (D), R507.2, TP506.1; also elsewhere on the board
SS_TSMS: Q506.3 (D), R518.2, TP512.1; also elsewhere on the board

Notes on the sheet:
SHUTDOWN SENSING
